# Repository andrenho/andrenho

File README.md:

Welcome!

<!--
**andrenho/andrenho** is a ✨ _special_ ✨ repository because its `README.md` (this file) appears on your GitHub profile.

Here are some ideas to get you started:

- 🔭 I’m currently working on ...
- 🌱 I’m currently learning ...
- 👯 I’m looking to collaborate on ...
- 🤔 I’m looking for help with ...
- 💬 Ask me about ...
- 📫 How to reach me: ...
- 😄 Pronouns: ...
- ⚡ Fun fact: ...
-->

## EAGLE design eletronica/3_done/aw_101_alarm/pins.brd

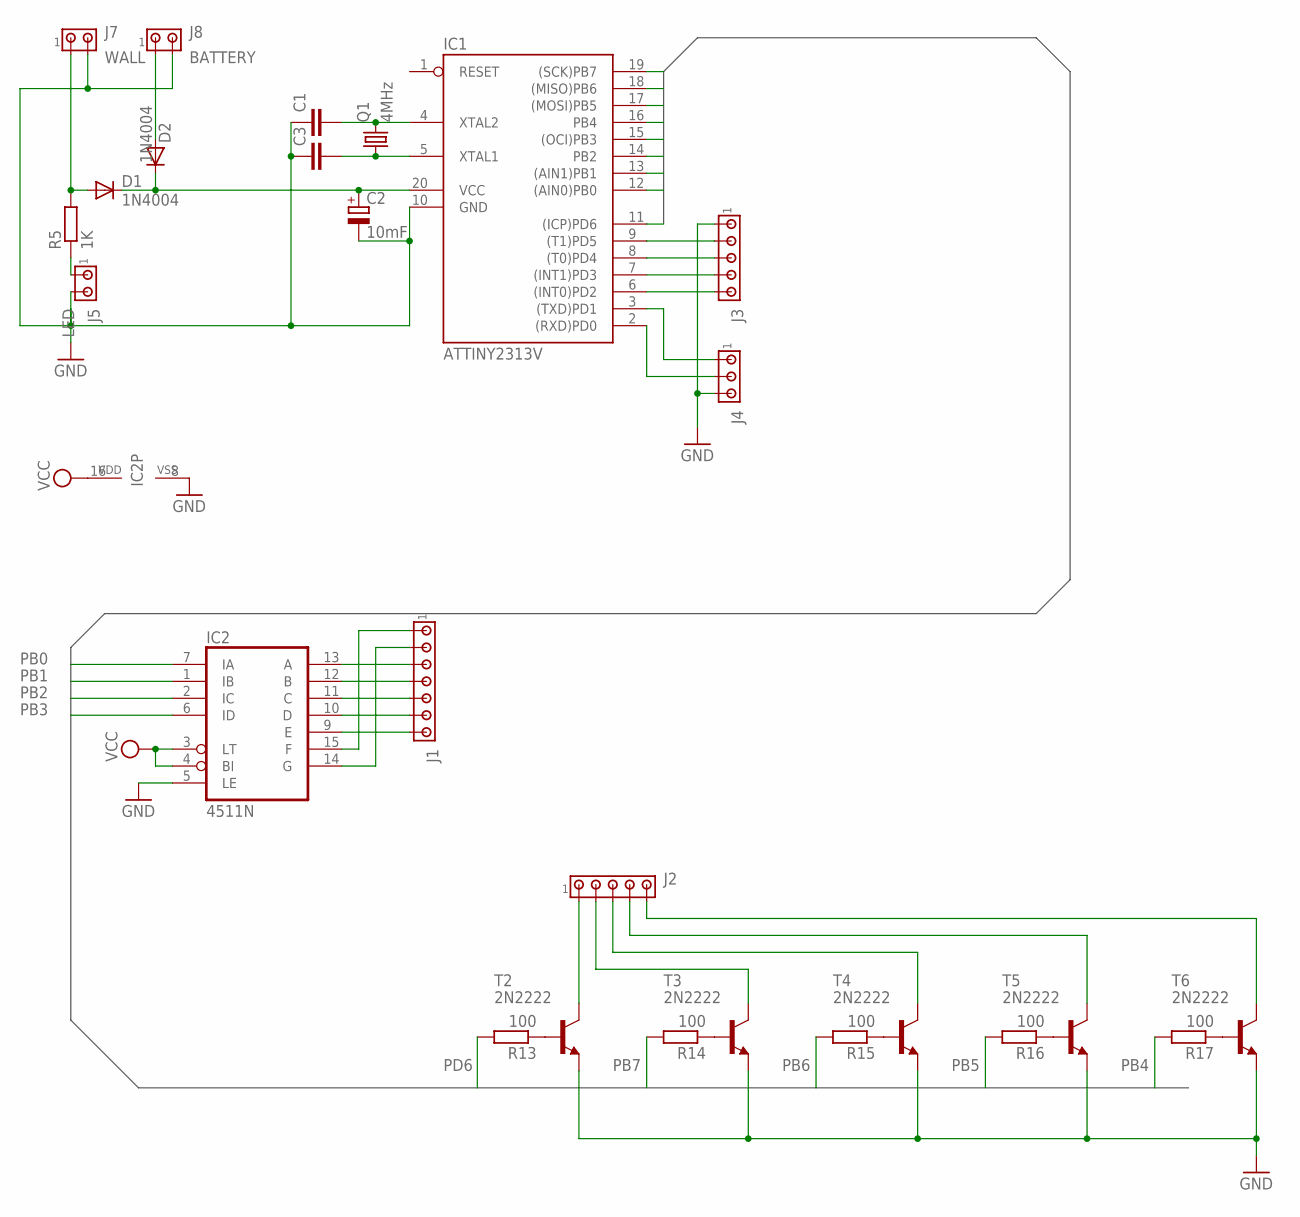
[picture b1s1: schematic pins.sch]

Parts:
C1, C3: C-EU025-025X050; C025-025X050
C2: 10mF; E2,5-6
D1, D2: 1N4004; DO41-10
IC1: ATTINY2313V; DIL20
IC2: 4511N; DIL16
J1: MTA07-100; 10X07MTA
J2, J3: MTA05-100; 10X05MTA
J4: MTA03-100; 10X03MTA
J5: LED; 10X02MTA
J7: WALL; 10X02MTA
J8: BATTERY; 10X02MTA
Q1: 4MHz; HC49U70
R5: 1K; 0207/10
R13, R14, R15, R16, R17: 100; 0207/10
T2, T3, T4, T5, T6: 2N2222; TO18

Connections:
GND: C1.1, C2.-, C3.1, IC1.10 (GND), IC2.5 (LE), IC2.8 (VSS), J3.1, J4.3, J5.2, J7.2, J8.2, T2.1 (E), T3.1 (E), T4.1 (E), T5.1 (E), T6.1 (E)
unnamed: IC1.9 ((T1)PD5), J3.2
unnamed: D1.A, J7.1, R5.2
unnamed: IC2.13 (A), J1.3
unnamed: IC2.12 (B), J1.4
unnamed: C3.2, IC1.5 (XTAL1), Q1.1
unnamed: IC1.8 ((T0)PD4), J3.3
unnamed: IC1.7 ((INT1)PD3), J3.4
unnamed: IC1.6 ((INT0)PD2), J3.5
unnamed: IC1.2 ((RXD)PD0), J4.2
unnamed: IC1.3 ((TXD)PD1), J4.1
unnamed: C1.2, IC1.4 (XTAL2), Q1.2
unnamed: D2.A, J8.1
unnamed: J2.1, T2.3 (C)
unnamed: J2.2, T3.3 (C)
unnamed: IC2.11 (C), J1.5
unnamed: IC2.10 (D), J1.6
unnamed: IC2.9 (E), J1.7
unnamed: IC2.15 (F), J1.1
unnamed: IC2.14 (G), J1.2
unnamed: J5.1, R5.1
unnamed: J2.3, T4.3 (C)
unnamed: J2.4, T5.3 (C)
unnamed: J2.5, T6.3 (C)
unnamed: R13.1, T2.2 (B)
unnamed: R14.1, T3.2 (B)
unnamed: R15.1, T4.2 (B)
unnamed: R16.1, T5.2 (B)
unnamed: R17.1, T6.2 (B)
PB0: IC1.12 ((AIN0)PB0), IC2.7 (IA)
PB1: IC1.13 ((AIN1)PB1), IC2.1 (IB)
PB2: IC1.14 (PB2), IC2.2 (IC)
PB3: IC1.15 ((OCI)PB3), IC2.6 (ID)
PB4: IC1.16 (PB4), R17.2
PB5: IC1.17 ((MOSI)PB5), R16.2
PB6: IC1.18 ((MISO)PB6), R15.2
PB7: IC1.19 ((SCK)PB7), R14.2
PD6: IC1.11 ((ICP)PD6), R13.2
VCC: C2.+, D1.C, D2.C, IC1.20 (VCC), IC2.3 (LT), IC2.4 (BI), IC2.16 (VDD)

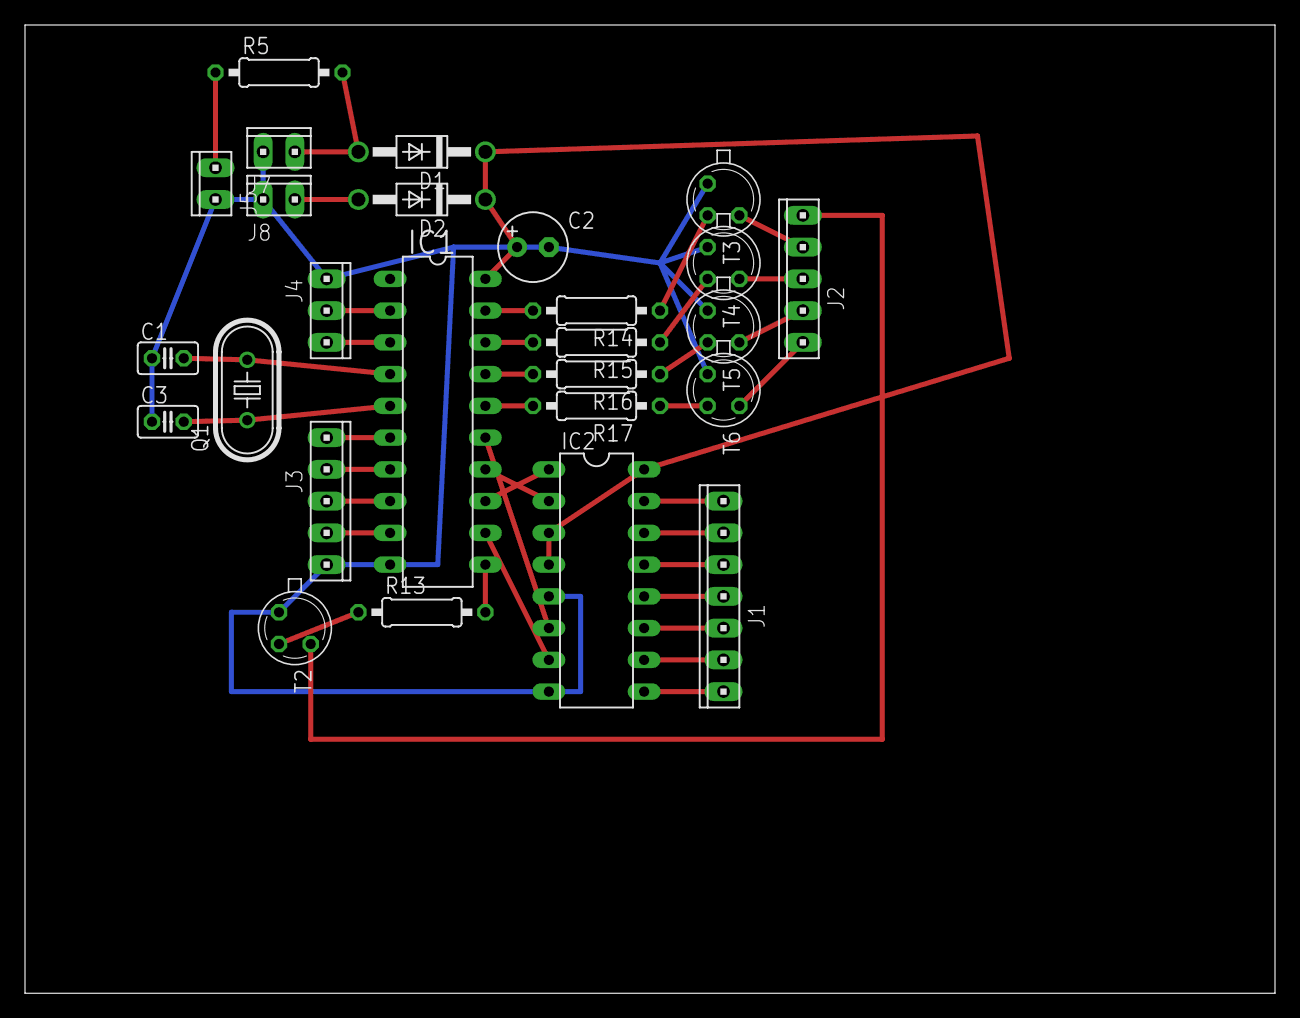
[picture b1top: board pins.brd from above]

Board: 2 copper layers, 100.0 x 77.5 mm, 26 parts (0 on the bottom side), 39 nets.

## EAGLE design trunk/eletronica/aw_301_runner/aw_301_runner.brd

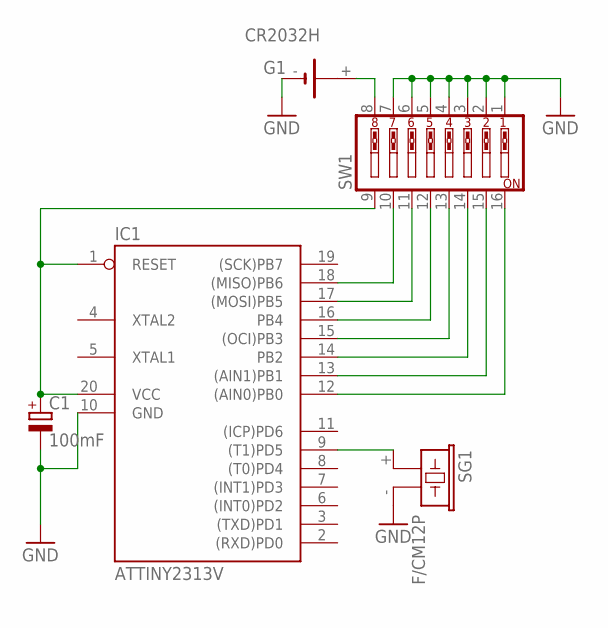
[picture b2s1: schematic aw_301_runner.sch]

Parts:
C1: 100mF; E2,5-6
G1: CR2032H
IC1: ATTINY2313V; DIL20
SG1: F/CM12P
SW1: SW_DIP-8; EDG-08

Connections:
GND: C1.-, G1.-, IC1.10 (GND), SG1.- (2), SW1.1, SW1.2, SW1.3, SW1.4, SW1.5, SW1.6, SW1.7
unnamed: IC1.9 ((T1)PD5), SG1.+ (1)
unnamed: IC1.12 ((AIN0)PB0), SW1.16
unnamed: C1.+, IC1.1 (RESET), IC1.20 (VCC), SW1.9
unnamed: IC1.13 ((AIN1)PB1), SW1.15
unnamed: IC1.14 (PB2), SW1.14
unnamed: IC1.15 ((OCI)PB3), SW1.13
unnamed: IC1.16 (PB4), SW1.12
unnamed: IC1.17 ((MOSI)PB5), SW1.11
unnamed: IC1.18 ((MISO)PB6), SW1.10
VCC: G1.+, SW1.8

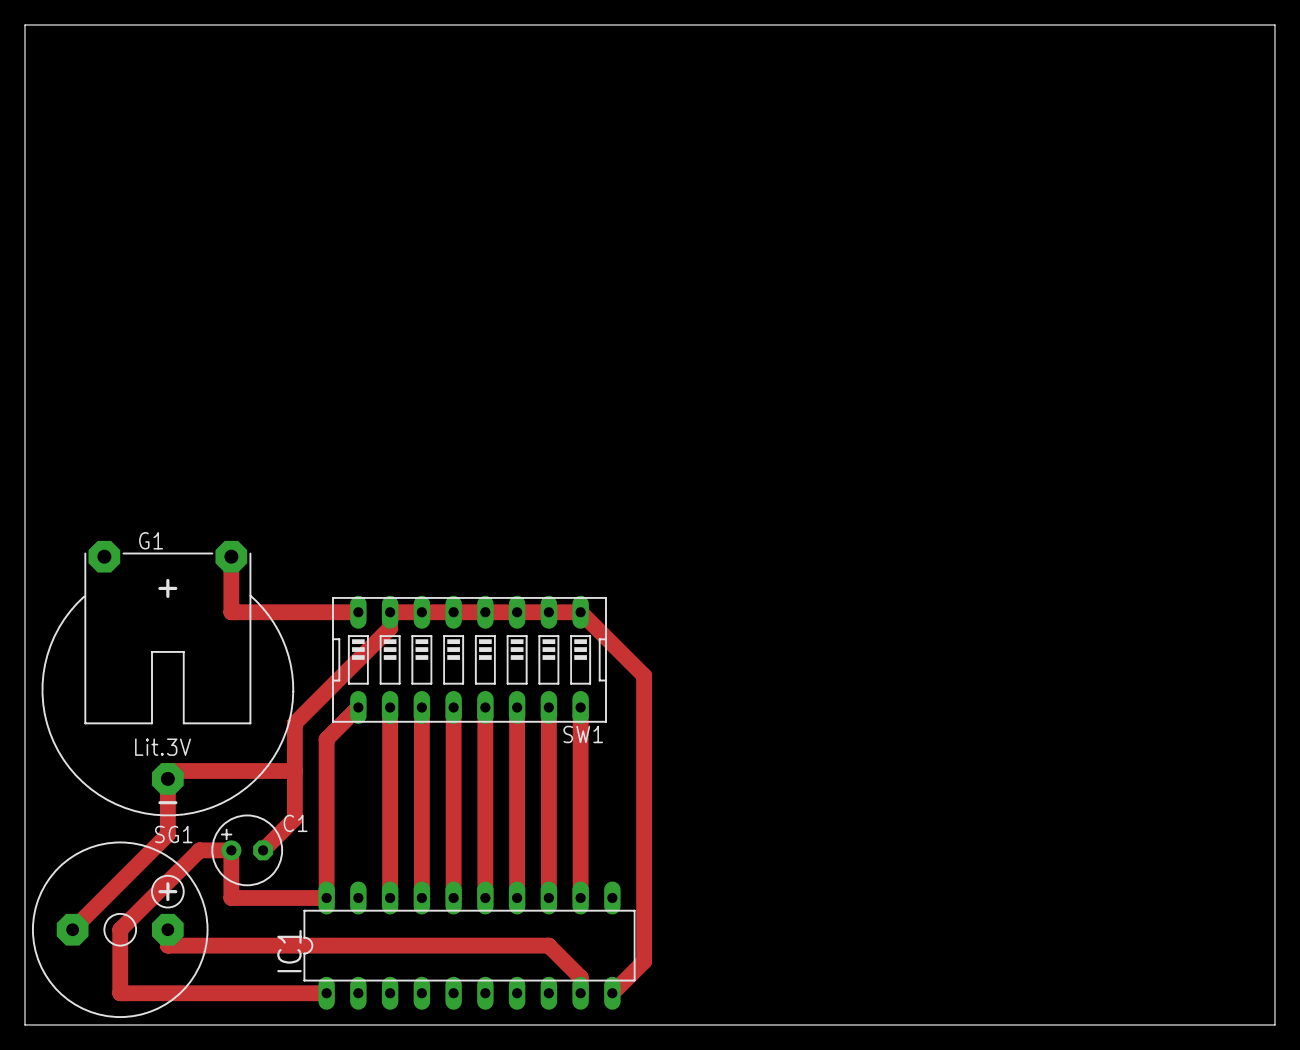
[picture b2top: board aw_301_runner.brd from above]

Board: 2 copper layers, 100.0 x 80.0 mm, 5 parts (0 on the bottom side), 11 nets.

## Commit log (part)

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2015-03-16 Migrating wiki contents from Google Code
